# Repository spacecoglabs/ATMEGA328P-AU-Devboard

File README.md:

# ATMEGA328P-AU-Devboard
A simple KiCADv6 design for a ATMEGA328P-AU Development Board

## Overview 
This repository contains a simple KiCADv6 design for a ATMEGA328P-AU development board. All pins are broken out to headers for prototyping use, with a few exceptions. This design includes an external 16MHz oscillator, power indicator LED, and user controllable LED. The form factor of the board was designed to be as small as possible, without compromising usability. Power can be supplied through the screw terminal, or directly through the various 5V and GND pins.

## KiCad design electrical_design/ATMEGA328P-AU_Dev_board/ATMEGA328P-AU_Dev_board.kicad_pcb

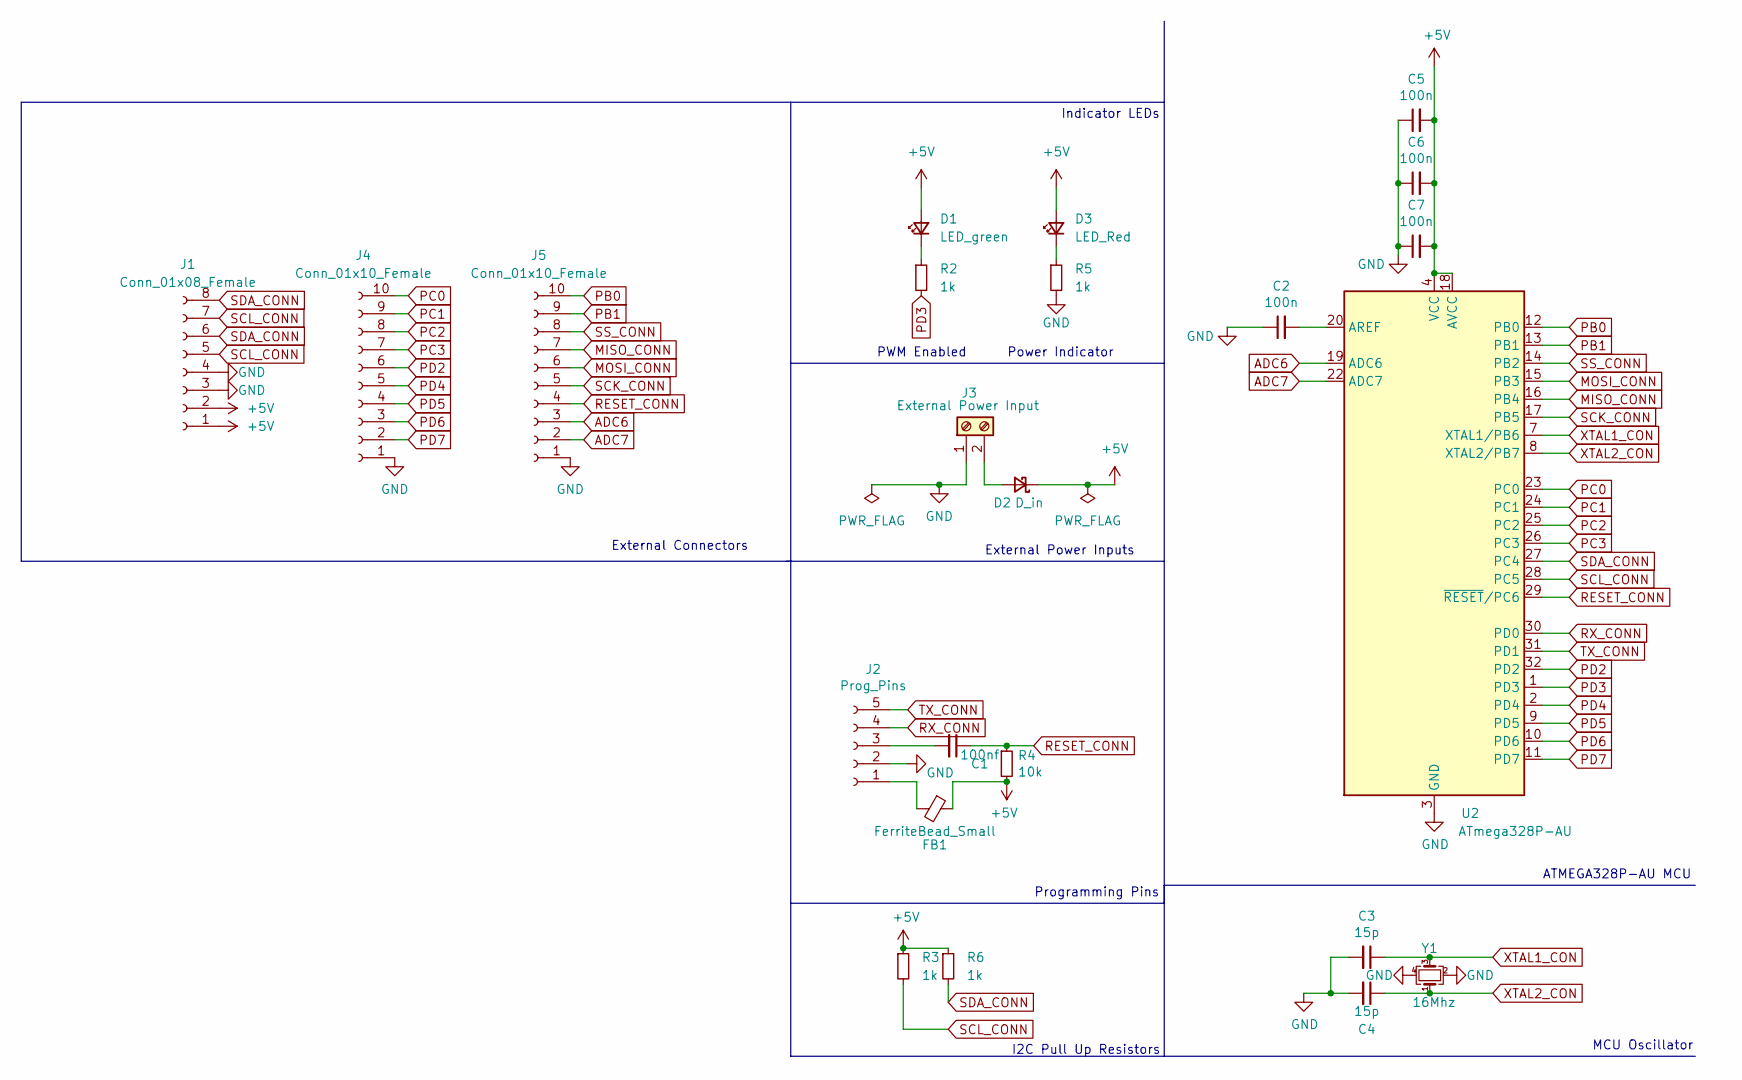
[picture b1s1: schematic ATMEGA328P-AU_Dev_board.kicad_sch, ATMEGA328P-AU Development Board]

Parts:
C1: 100nf; C_0603_1608Metric; LCSC C14663
C2, C5, C6, C7: 100n; C_0603_1608Metric; LCSC C14663
C3, C4: 15p; C_0603_1608Metric; LCSC C1644
D1: LED_green; LED_0805_2012Metric; LCSC C2297
D2: D_in; D_SOD-123; LCSC C8598
D3: LED_Red; LED_0603_1608Metric; LCSC C2286
FB1: FerriteBead_Small; L_0805_2012Metric; LCSC C96710
J1: Conn_01x08_Female; Conn_8
J2: Prog_Pins; Conn_5
J3: External Power Input; two_pin_screw_term
J4, J5: Conn_01x10_Female; Conn_10
R2, R3, R5, R6: 1k; R_1206_3216Metric; LCSC C4410
R4: 10k; R_0603_1608Metric; LCSC C25804
U2: ATmega328P-AU; TQFP-32_7x7mm_P0.8mm; LCSC C14877
Y1: 16Mhz; Crystal_SMD_2520-4Pin_2.5x2.0mm; LCSC C284159

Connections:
+5V: C5.2, C6.2, C7.2, D1.2 (A), D2.1 (K), D3.2 (A), FB1.1, J1.1, J1.2, R3.1, R4.2, R6.1, U2.4 (VCC), U2.6 (VCC), U2.18 (AVCC)
ADC6: J5.3, U2.19 (ADC6)
ADC7: J5.2, U2.22 (ADC7)
GND: C2.1, C3.2, C4.2, C5.1, C6.1, C7.1, J1.3, J1.4, J2.2, J3.1, J4.1, J5.1, R5.2, U2.3 (GND), U2.5 (GND), U2.21 (GND), Y1.2, Y1.4
MISO_CONN: J5.7, U2.16 (PB4)
MOSI_CONN: J5.6, U2.15 (PB3)
unnamed: C1.2, J2.3
unnamed: C2.2, U2.20 (AREF)
unnamed: D1.1 (K), R2.1
unnamed: D2.2 (A), J3.2
unnamed: D3.1 (K), R5.1
unnamed: FB1.2, J2.1
PB0: J5.10, U2.12 (PB0)
PB1: J5.9, U2.13 (PB1)
PC0: J4.10, U2.23 (PC0)
PC1: J4.9, U2.24 (PC1)
PC2: J4.8, U2.25 (PC2)
PC3: J4.7, U2.26 (PC3)
PD2: J4.6, U2.32 (PD2)
PD3: R2.2, U2.1 (PD3)
PD4: J4.5, U2.2 (PD4)
PD5: J4.4, U2.9 (PD5)
PD6: J4.3, U2.10 (PD6)
PD7: J4.2, U2.11 (PD7)
RESET_CONN: C1.1, J5.4, R4.1, U2.29 (~RESET/PC6)
RX_CONN: J2.4, U2.30 (PD0)
SCK_CONN: J5.5, U2.17 (PB5)
SCL_CONN: J1.5, J1.7, R3.2, U2.28 (PC5)
SDA_CONN: J1.6, J1.8, R6.2, U2.27 (PC4)
SS_CONN: J5.8, U2.14 (PB2)
TX_CONN: J2.5, U2.31 (PD1)
XTAL1_CON: C3.1, U2.7 (XTAL1/PB6), Y1.3
XTAL2_CON: C4.1, U2.8 (XTAL2/PB7), Y1.1

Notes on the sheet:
MCU Oscillator
PWM Enabled
ATMEGA328P-AU MCU
External Connectors
Power Indicator
External Power Inputs
Indicator LEDs
I2C Pull Up Resistors
Programming Pins

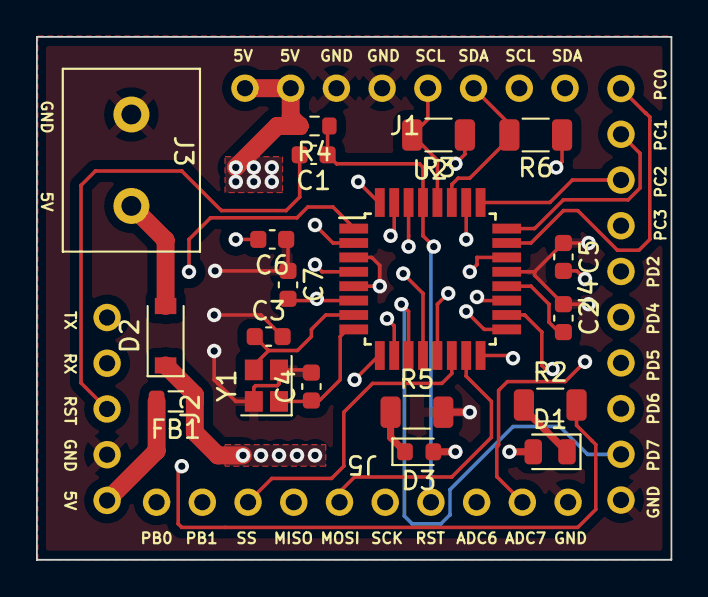
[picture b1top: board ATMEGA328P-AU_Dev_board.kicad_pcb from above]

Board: 4 copper layers, 35.2 x 29.0 mm, 23 parts (0 on the bottom side), 33 nets.

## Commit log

2024-03-03 initial commit of electrical design
2024-03-03 add links to images in docs
2024-03-03 shrink images
2024-03-03 shrink images again
